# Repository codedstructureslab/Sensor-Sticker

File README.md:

# Sensor-Sticker

Minimal hardware for distributed sensing in aircraft, etc.

## Version

**Version 0:** 
* Minimal sensor size, irregular boards
* Ordered 2016-12-30

**Version 1:** 
* Constant sensor button size
* (TODO) Ensure that distance between connector edge and sensor centerpoint is 1.7 mm
* (TODO) Redo jtag pinout for Atmel ICE programmer
* Redo DSP310 Pinout to make assembly clearer

**Version 2:**
* ATSAMD11 Output?

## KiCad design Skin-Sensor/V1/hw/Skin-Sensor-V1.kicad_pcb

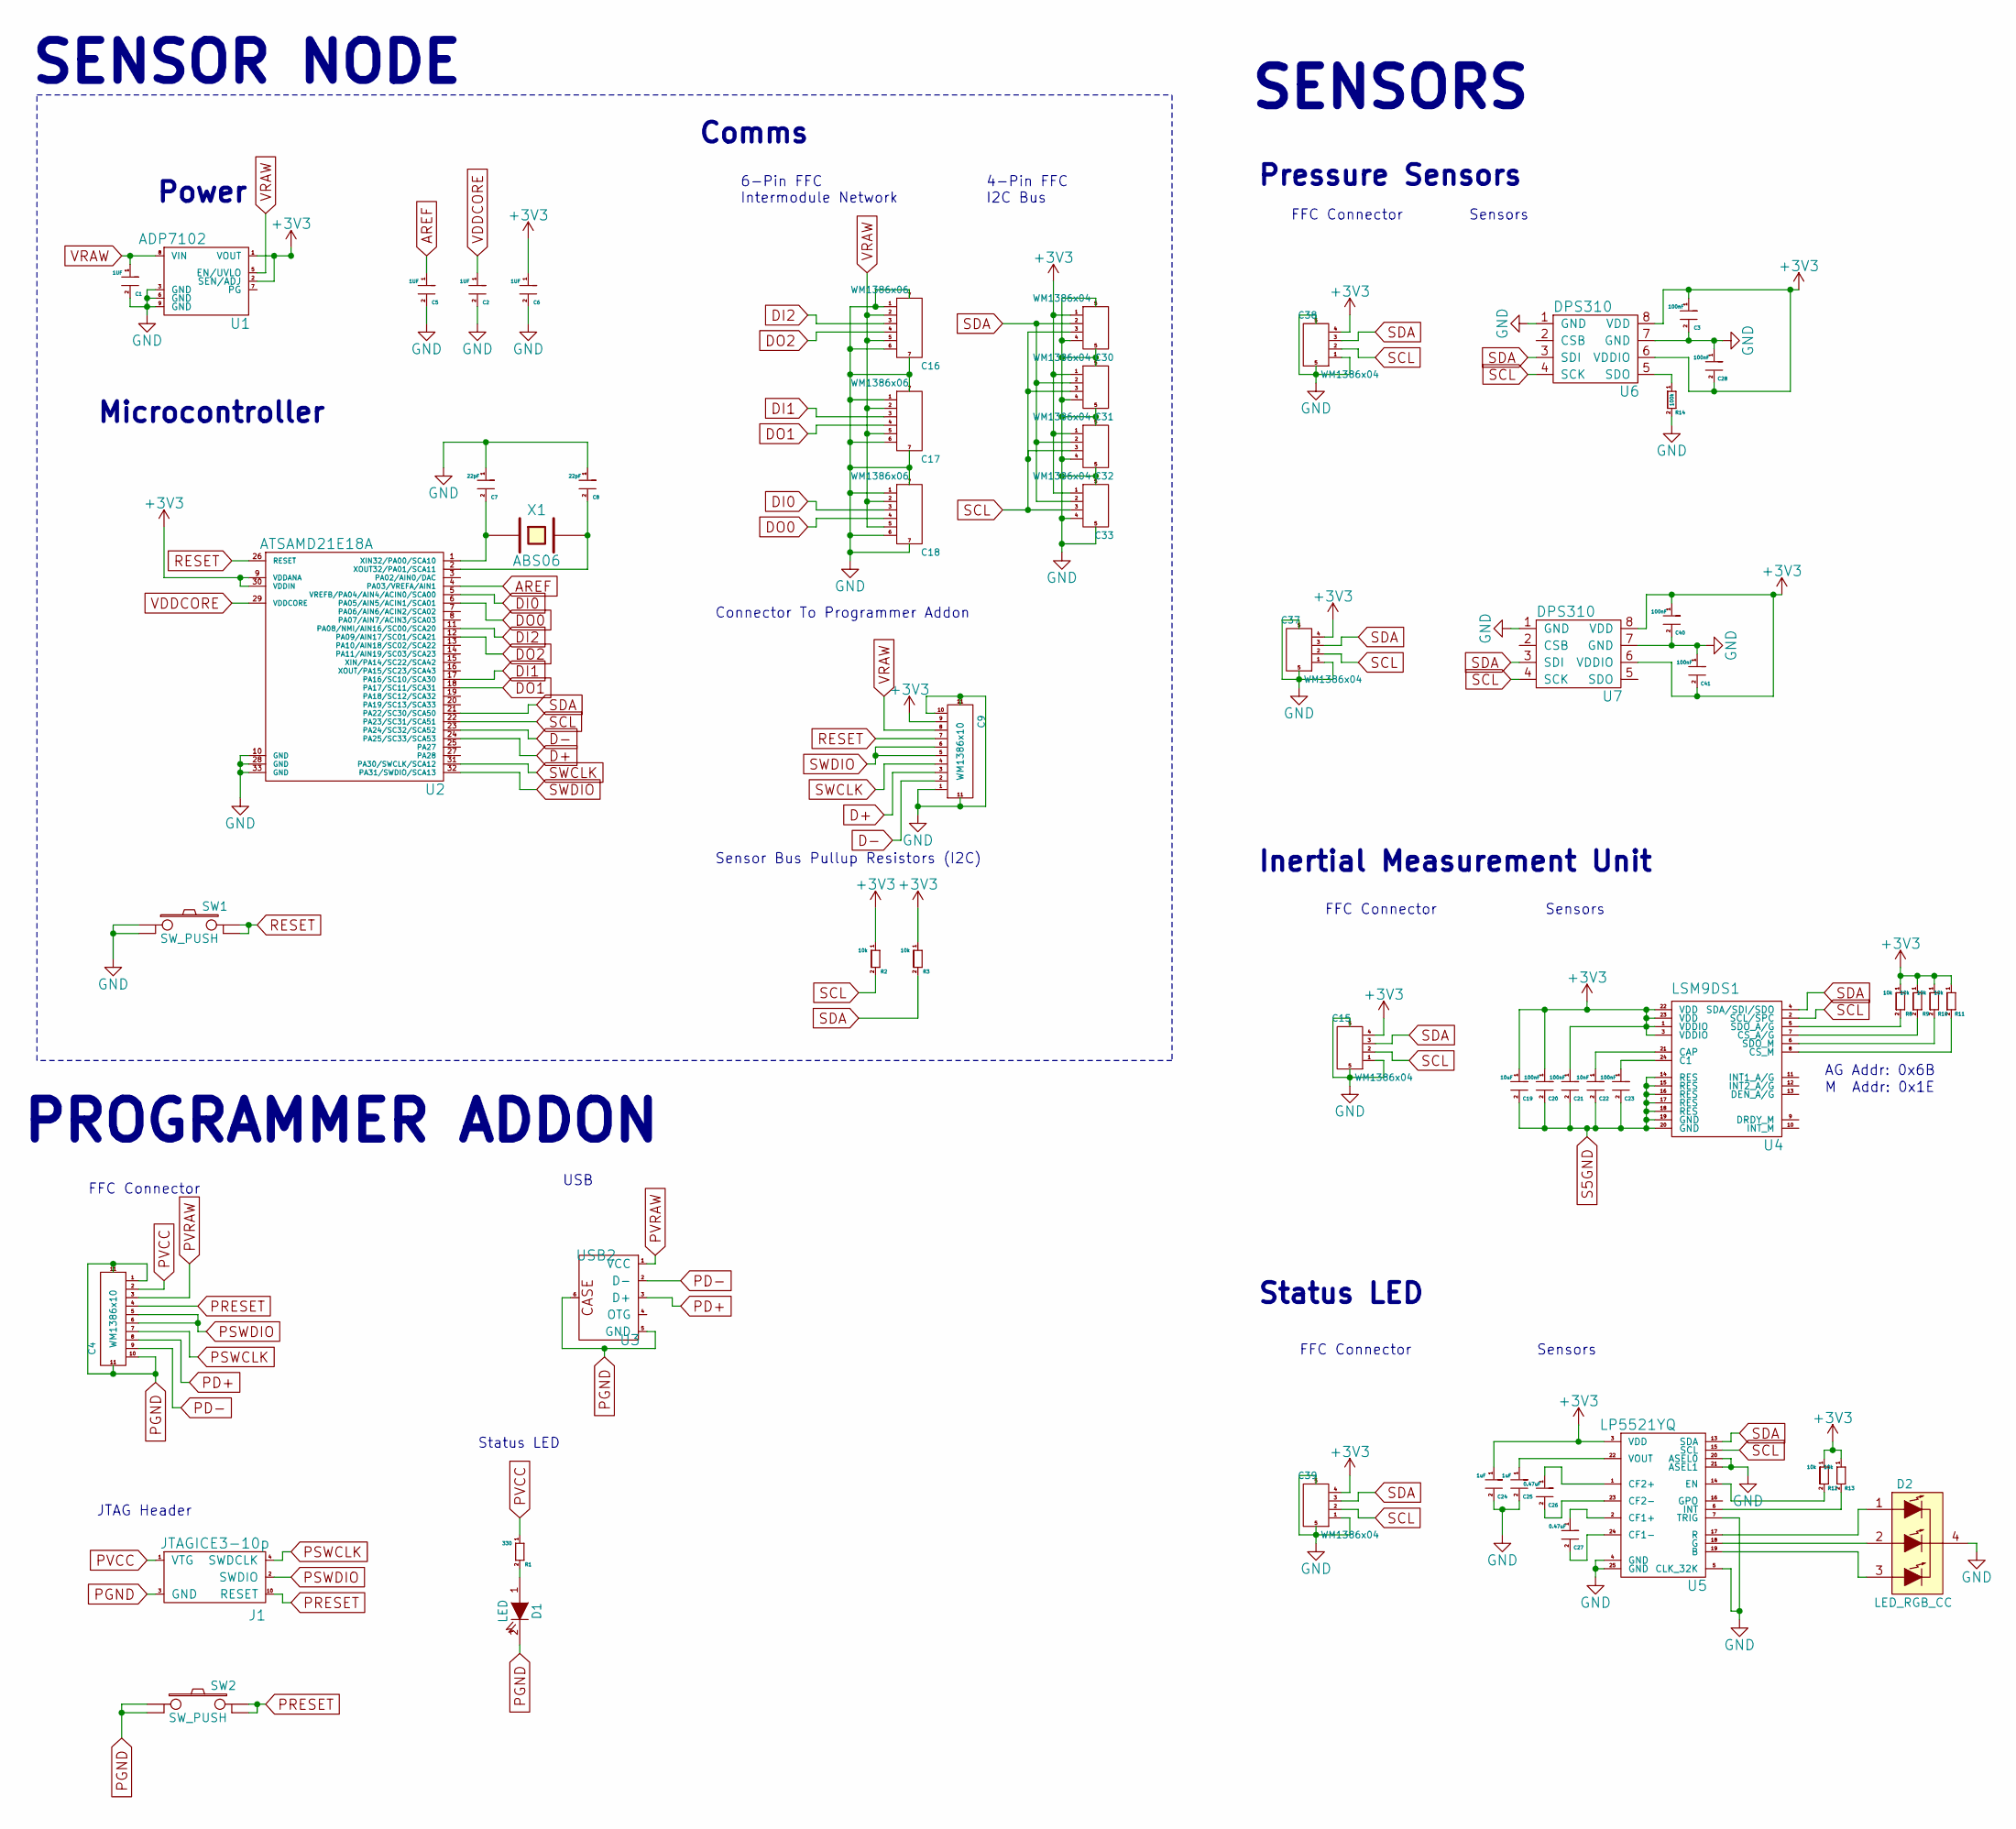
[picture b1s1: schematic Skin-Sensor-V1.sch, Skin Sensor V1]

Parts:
C1, C2, C5, C6: 1UF; C_0402
C3, C20, C21, C23, C28, C40, C41: 100nF; C_0402
C4, C9: WM1386x10; WM1387x10-REC
C7, C8: 22pF; C_0402
C15, C30, C31, C32, C33, C37, C38, C39: WM1386x04; WM1386x04-REC
C16, C17, C18: WM1386x06; WM1387x06-REC
C19: 10uF; C_0402
C22: 10nF; C_0402
C24, C25: 1uF; C_0402
C26, C27: 0.47uF; C_0402
D1: LED; LED_0402
D2: LED_RGB_CC; 4-PLCC
J1: JTAGICE3-10p
R1: 330; R_0402
R2, R3, R8, R9, R10, R11, R12, R13: 10k; R_0402
R14: 100k; R_0402
SW1, SW2: SW_PUSH; 4-PLCC
U1: ADP7102; DFN-8-1EP_3x3mm_Pitch0.5mm
U2: ATSAMD21E18A; QFN-32-1EP_5x5mm_Pitch0.5mm
U3: USB2; USBMICRO-10104110
U4: LSM9DS1
U5: LP5521YQ; QFN-24-1EP_4x5mm_Pitch0.5mm
U6, U7: DPS310; 8-LGA
X1: ABS06

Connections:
+3V3: C3.1, C6.1, C9.9, C15.4, C19.1, C20.1, C21.1, C24.1, C28.2, C30.1, C31.1, C32.1, C33.1, C37.4, C38.4, C39.4, C40.1, C41.2, R2.1, R3.1, R8.1, R9.1, R10.1, R11.1, R12.1, R13.1, U1.1 (VOUT), U1.2 (SEN/ADJ), U2.9 (VDDANA), U2.30 (VDDIN), U4.1 (VDDIO), U4.3 (VDDIO), U4.22 (VDD), U4.23 (VDD), U5.3 (VDD), U6.6 (VDDIO), U6.8 (VDD), U7.6 (VDDIO), U7.8 (VDD)
AREF: C5.1, U2.4 (PA03/VREFA/AIN1)
D+: C9.3, U2.24 (PA25/SC33/SCA53)
D-: C9.2, U2.23 (PA24/SC32/SCA52)
DI0: C18.3, U2.5 (VREFB/PA04/AIN4/ACIN0/SCA00)
DI1: C17.3, U2.17 (PA16/SC10/SCA30)
DI2: C16.3, U2.11 (PA08/NMI/AIN16/SC00/SCA20)
DO0: C18.4, U2.6 (PA05/AIN5/ACIN1/SCA01)
DO1: C17.4, U2.18 (PA17/SC11/SCA31)
DO2: C16.4, U2.12 (PA09/AIN17/SC01/SCA21)
GND: C1.2, C2.2, C3.2, C5.2, C6.2, C7.1, C8.1, C9.1, C9.10, C9.11, C15.1, C15.5, C16.1, C16.6, C16.7, C17.1, C17.6, C17.7, C18.1, C18.6, C18.7, C24.2, C25.2, C28.1, C30.4, C30.5, C31.4, C31.5, C32.4, C32.5, C33.4, C33.5, C37.1, C37.5, C38.1, C38.5, C39.1, C39.5, C40.2, C41.1, D2.4 (COMMON_CATHODE), R14.2, SW1.1, SW1.2, U1.3 (GND), U1.6 (GND), U1.9 (GND), U2.10 (GND), U2.28 (GND), U2.33 (GND), U5.4 (GND), U5.5 (CLK_32K), U5.7 (TRIG), U5.20 (ASEL0), U5.21 (ASEL1), U5.25 (GND), U6.1 (GND), U6.7 (GND), U7.1 (GND), U7.7 (GND)
unnamed: C7.2, U2.1 (XIN32/PA00/SCA10), X1.1
unnamed: C8.2, U2.2 (XOUT32/PA01/SCA11), X1.2
unnamed: C22.1, U4.21 (CAP)
unnamed: C23.1, U4.24 (C1)
unnamed: C25.1, U5.22 (VOUT)
unnamed: C26.1, U5.1 (CF2+)
unnamed: C26.2, U5.23 (CF2-)
unnamed: C27.1, U5.2 (CF1+)
unnamed: C27.2, U5.24 (CF1-)
unnamed: D1.1 (A), R1.2
unnamed: D2.1 (RED_ANODE), U5.17 (R)
unnamed: D2.2 (GREEN_ANODE), U5.18 (G)
unnamed: D2.3 (BLUE_ANODE), U5.19 (B)
unnamed: R8.2, U4.5 (SDO_A/G)
unnamed: R9.2, U4.7 (CS_A/G)
unnamed: R10.2, U4.6 (SDO_M)
unnamed: R11.2, U4.8 (CS_M)
unnamed: R12.2, U5.14 (EN)
unnamed: R13.2, U5.6 (INT)
unnamed: R14.1, U6.5 (SDO)
PD+: C4.8, U3.3 (D+)
PD-: C4.9, U3.2 (D-)
PGND: C4.1, C4.10, C4.11, D1.2 (K), J1.3 (GND), SW2.1, SW2.2, U3.5 (GND), U3.6
PRESET: C4.4, J1.10 (RESET), SW2.3, SW2.4
PSWCLK: C4.7, J1.4 (SWDCLK)
PSWDIO: C4.5, C4.6, J1.2 (SWDIO)
PVCC: C4.2, J1.1 (VTG), R1.1
PVRAW: C4.3, U3.1 (VCC)
RESET: C9.7, SW1.3, SW1.4, U2.26 (RESET)
S5GND: C19.2, C20.2, C21.2, C22.2, C23.2, U4.14 (RES), U4.15 (RES), U4.16 (RES), U4.17 (RES), U4.18 (RES), U4.19 (GND), U4.20 (GND)
SCL: C15.2, C30.3, C31.3, C32.3, C33.3, C37.2, C38.2, C39.2, R2.2, U2.22 (PA23/SC31/SCA51), U4.2 (SCL/SPC), U5.15 (SCL), U6.4 (SCK), U7.4 (SCK)
SDA: C15.3, C30.2, C31.2, C32.2, C33.2, C37.3, C38.3, C39.3, R3.2, U2.21 (PA22/SC30/SCA50), U4.4 (SDA/SDI/SDO), U5.13 (SDA), U6.3 (SDI), U7.3 (SDI)
SWCLK: C9.4, U2.31 (PA30/SWCLK/SCA12)
SWDIO: C9.5, C9.6, U2.32 (PA31/SWDIO/SCA13)
VDDCORE: C2.1, U2.29 (VDDCORE)
VRAW: C1.1, C9.8, C16.2, C16.5, C17.2, C17.5, C18.2, C18.5, U1.5 (EN/UVLO), U1.8 (VIN)

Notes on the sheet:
Power
Microcontroller
Comms
SENSORS
Status LED
AG Addr: 0x6B
M Addr: 0x1E
SENSOR NODE
PROGRAMMER ADDON
6-Pin FFC Intermodule Network
Sensor Bus Pullup Resistors (I2C)
Connector To Programmer Addon
JTAG Header
USB
FFC Connector
Sensors
Pressure Sensors
Inertial Measurement Unit
4-Pin FFC I2C Bus

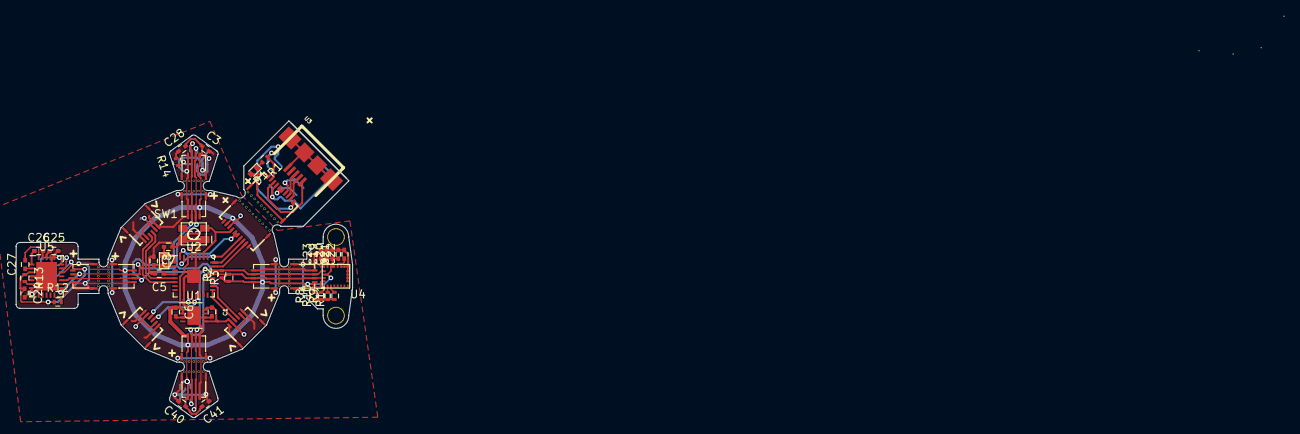
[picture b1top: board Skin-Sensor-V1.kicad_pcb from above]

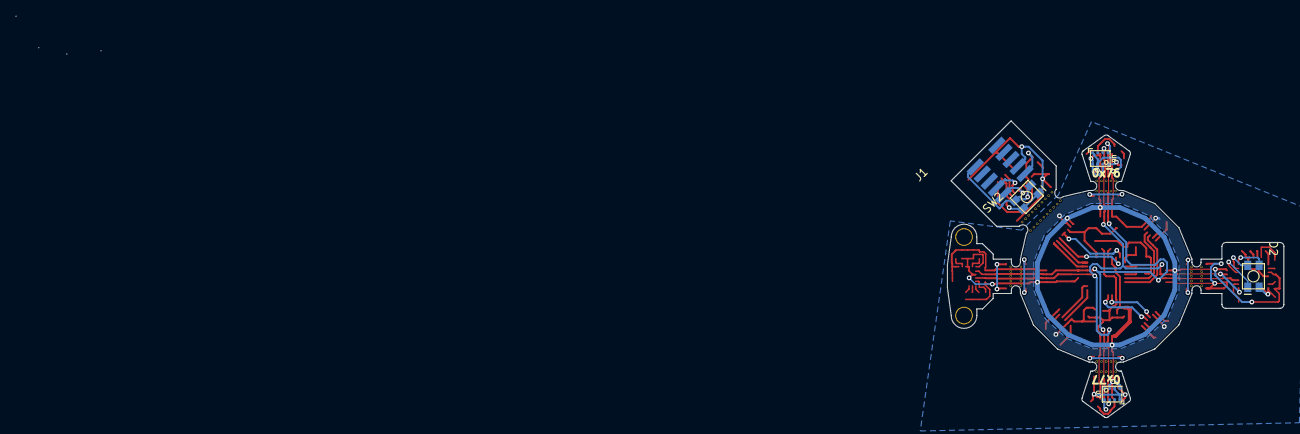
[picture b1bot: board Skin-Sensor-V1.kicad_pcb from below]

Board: 2 copper layers, 161.4 x 51.1 mm, 55 parts (5 on the bottom side), 47 nets.

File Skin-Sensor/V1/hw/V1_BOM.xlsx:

Reference Designator | Quantity | Description/Value | Manufacturer Part Number (MPN)
C1,C2,C5,C6,C24,C25 | 6 | 0402 Cer Cap 1uF | C1005X5R1V105K050BC
C7,C8 | 2 | 0402 Cer Cap 22pF | CBR04C220F5GAC
C4,C9 | 2 | Wm1389 Plug (10) | 5034801000
C3,C20,C21,C23,C28,C40,C41 | 7 | 0402 Cer Cap 100nF | GRM155R71C104KA88J
C19 | 1 | 0402 Cer Cap 10uF | CL05A106MP8NUB8
C22 | 1 | 0402 Cer Cap 10nF | GRM155R71H103KA88D
C26,C27 | 2 | 0402 Cer Cap 0.47uF | C1005X5R1E474K050BB
R1 | 1 | 0402 Res 330 | RC0402JR-07330RL
R2,R3,R8,R9,R10,R11,R12,R13 | 8 | 0402 Res 10k | RC0402JR-0710KL
R14 | 1 | 0402 Res 100k | RC0402JR-07100KL
D1 | 1 | 0402 LED | LNJ247W82RA
D2 | 1 | RGB LED Common Cathode | XZM2CRKM2DGFBB45SCCB
C15,C30,C31,C32,C33,C37,C38,C39 | 8 | WM1386 Plug | 5034800400
C16,C17,C18 | 3 | WM1387 Plug | 5034800600
SW1,SW2 | 2 | Switch | TL3700AF100QG
J1 | 1 | 5x2 Header JTAG 0.05" | 20021121-00010C4LF
U1 | 1 | ADP7102 3.3V Reg | ADP7102ACPZ-3.3-R7
U2 | 1 | ATSAMD21E18A uP | ATSAMD21E18A-MFT
U3 | 1 | USBMICRO | 10104110-0001LF
U4 | 1 | LSM9DS1 IMU | LSM9DS1TR
U5 | 1 | LP5521YQ LED Driver | LP5521YQ/NOPB
U6,U7 | 2 | DPS310 Pressure Sensor | DPS310XTSA1
X1 | 1 | 32.768kHz Crystal | ABS06-32.768KHZ-1-T

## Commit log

2017-01-04 Added V0, V1 boards
2017-01-04 Added documentation .dwg
2017-01-09 Skin Sensor Dump
2017-01-09 improved instructions
2017-01-11 updated TODO
2017-01-20 V1 rev, in all its glory
